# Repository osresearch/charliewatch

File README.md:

"Analog" watch with 60+12 Charlieplexed LEDs. Based on Travis Goodspeed's
GoodWatch21 schematic, using the CC430F5137IRGZR CPU, which doesn't
have the LCD controller of the CC430F6xxx in the GoodWatch. There are
also pads for a six pin EZfet cable with pogopins for programming or
serial communication.

v0.2 works, although it has no radio parts.  It is exactly 1 square inch
of PCB and should fit in a 38mm or 36mm case.

v0.1 works, although the radio parts have not been tested.  It is a slightly
larger board and fits in a 40mm case.

[Charliewtch schematic](datasheets/charliewatch.pdf)

Building the firmware
-----

Note: some other system packages (boost libraries?) might also be needed.

First, get the toolchain (msp430-gcc):

    sudo apt install gcc-msp430 mspdebug

Then the all-important lib file (from https://www.ti.com/tool/MSPDS):

    sudo apt install libhidapi-dev
    mkdir MSPDebugStack
    wget https://software-dl.ti.com/msp430/msp430_public_sw/mcu/msp430/MSPDS/3_15_1_001/export/MSPDebugStack_OS_Package_3_15_1_1.zip

Copy in the hidapi header (WTFBBQ):

    cp /usr/include/hidapi/hidapi.h ThirdParty/include/

Copy the following into a file 'hidapi.patch', so we can use the system hidapi library:

    --- Makefile    2020-12-18 18:01:18.602942502 +0100
    +++ Makefile.new    2020-12-18 18:02:58.472096541 +0100
    @@ -123,7 +123,7 @@
     OBJS := $(patsubst %.cpp, %.o, $(SRC))
    
     all: $(BSLLIB) $(OBJS)
    -   $(CXX) $(CXXFLAGS) -shared $(OUTNAME)$(OUTPUT) -o $(OUTPUT) $(OBJS) $(HIDOBJ) $(LIBDIRS) $(BSTATIC) $(STATIC_LIBS) $(BDYNAMIC) $(LIBS)
    +   $(CXX) $(CXXFLAGS) -shared $(OUTNAME)$(OUTPUT) -o $(OUTPUT) $(OBJS) -lhidapi-libusb $(LIBDIRS) $(BSTATIC) $(STATIC_LIBS) $(BDYNAMIC) $(LIBS)
        rm -f $(STATICOUTPUT).a
        ar -rs $(STATICOUTPUT).a $(OBJS)

Then apply and make:

    patch < hidapi.patch
    make

Finally, build and flash the firmware:

    git clone https://github.com/osresearch/charliewatch.git
    cd charliewatch/firmware
    make
    export LD_LIBRARY_PATH=$LD_LIBRARY_PATH:`pwd`../../MSPDebugStack/
    mspdebug tilib "prog charliewatch.elf"

Programming cable
-----

From the top of the v0.1 board:
* RST / TDIO
* RXD on programmer
* TXD on programmer
* VCC
* TST / TCK
* GND

v0.2:
* greem
* white
* blue
* purple
* gray
* black

There is also a four-wire setup that might simplify the wiring.
Travis documents it and the power consumption here:
https://github.com/travisgoodspeed/goodwatch/wiki/EnergyTrace

Bricked Launchpad
-----

If you brick your launchpad by running Energia under Linux, it will no
longer program the Charliewatch.  The other weirdness is that `tilib`
can detect the device, but can't write to it unless run as root.

Energy Trace
----
* `libmsp430.so`: https://dlbeer.co.nz/articles/slac460y/index.html
* https://github.com/carrotIndustries/energytrace-util
* Have to update path to `MSP430.h` from the `slac/DLL430_v3/include` directory

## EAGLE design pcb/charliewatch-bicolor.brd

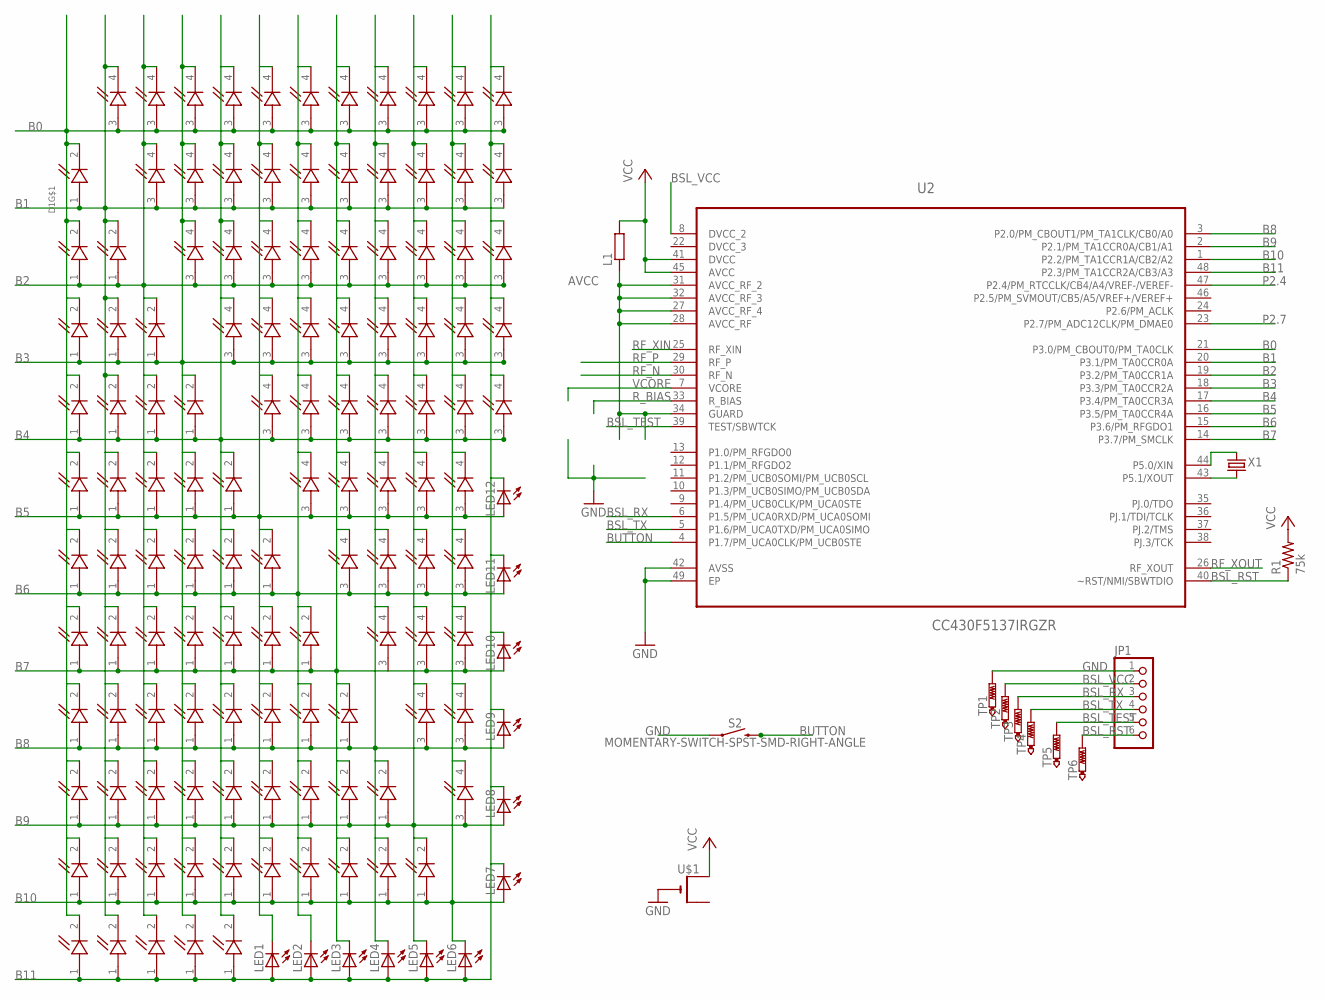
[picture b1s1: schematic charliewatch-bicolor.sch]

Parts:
D1, D2, D3, D4, D5, D6, D7, D8, D9, D10, D11, D12, D13, D14, D15, D16, D17, D18, D19, D20, D21, D22, D23, D24, D25, D26, D27, D28, D29, D30, D31, D32, D33, D34, D35, D36, D37, D38, D39, D40, D41, D42, D43, D44, D45, D46, D47, D48, D49, D50, D51, D52, D53, D54, D55, D56, D57, D58, D59, D60: APHB1608SYKSURKC; LED_APHB1608SYKSURKC
JP1: PINHD-1X6LOCK; 1X06-BIGLOCK
L1: R-EU_R0603; R0603
LED1, LED2, LED3, LED4, LED5, LED6, LED7, LED8, LED9, LED10, LED11, LED12: LEDCHIPLED_0805; CHIPLED_0805
R1: 75k; R0402
S2: MOMENTARY-SWITCH-SPST-SMD-RIGHT-ANGLE; TACTILE_SWITCH_SMD_RIGHT_ANGLE
TP1: PTR1TP10SQ; TP10SQ
TP2, TP3, TP4, TP5, TP6: PTR1TP10R; TP10R
U2: CC430F5137IRGZR; QFN50P700X700X100-49N
U$1: CR2032THM; CR2032-THRU
X1: CRYSTALS-NOGND-IQXC-25; 2.0X1.2-2PAD

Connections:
AVCC: L1.1, U2.27 (AVCC_RF_4), U2.28 (AVCC_RF), U2.31 (AVCC_RF_2), U2.32 (AVCC_RF_3), U2.34 (GUARD)
B0: D1.2 (Y_C), D1.3 (R_A), D2.2 (Y_C), D2.3 (R_A), D3.2 (Y_C), D3.3 (R_A), D5.2 (Y_C), D5.3 (R_A), D7.2 (Y_C), D7.3 (R_A), D10.2 (Y_C), D10.3 (R_A), D13.2 (Y_C), D13.3 (R_A), D17.2 (Y_C), D17.3 (R_A), D21.2 (Y_C), D21.3 (R_A), D26.2 (Y_C), D26.3 (R_A), D31.2 (Y_C), D31.3 (R_A), U2.21 (P3.0/PM_CBOUT0/PM_TA0CLK)
B1: D1.1 (Y_A), D1.4 (R_C), D4.2 (Y_C), D4.3 (R_A), D6.2 (Y_C), D6.3 (R_A), D8.2 (Y_C), D8.3 (R_A), D11.2 (Y_C), D11.3 (R_A), D14.2 (Y_C), D14.3 (R_A), D18.2 (Y_C), D18.3 (R_A), D22.2 (Y_C), D22.3 (R_A), D27.2 (Y_C), D27.3 (R_A), D32.2 (Y_C), D32.3 (R_A), D37.2 (Y_C), D37.3 (R_A), U2.20 (P3.1/PM_TA0CCR0A)
B2: D2.1 (Y_A), D2.4 (R_C), D4.1 (Y_A), D4.4 (R_C), D9.2 (Y_C), D9.3 (R_A), D12.2 (Y_C), D12.3 (R_A), D15.2 (Y_C), D15.3 (R_A), D19.2 (Y_C), D19.3 (R_A), D23.2 (Y_C), D23.3 (R_A), D28.2 (Y_C), D28.3 (R_A), D33.2 (Y_C), D33.3 (R_A), D38.2 (Y_C), D38.3 (R_A), D42.2 (Y_C), D42.3 (R_A), U2.19 (P3.2/PM_TA0CCR1A)
B3: D3.1 (Y_A), D3.4 (R_C), D6.1 (Y_A), D6.4 (R_C), D9.1 (Y_A), D9.4 (R_C), D16.2 (Y_C), D16.3 (R_A), D20.2 (Y_C), D20.3 (R_A), D24.2 (Y_C), D24.3 (R_A), D29.2 (Y_C), D29.3 (R_A), D34.2 (Y_C), D34.3 (R_A), D39.2 (Y_C), D39.3 (R_A), D43.2 (Y_C), D43.3 (R_A), D47.2 (Y_C), D47.3 (R_A), U2.18 (P3.3/PM_TA0CCR2A)
B4: D5.1 (Y_A), D5.4 (R_C), D8.1 (Y_A), D8.4 (R_C), D12.1 (Y_A), D12.4 (R_C), D16.1 (Y_A), D16.4 (R_C), D25.2 (Y_C), D25.3 (R_A), D30.2 (Y_C), D30.3 (R_A), D35.2 (Y_C), D35.3 (R_A), D40.2 (Y_C), D40.3 (R_A), D44.2 (Y_C), D44.3 (R_A), D48.2 (Y_C), D48.3 (R_A), D51.2 (Y_C), D51.3 (R_A), U2.17 (P3.4/PM_TA0CCR3A)
B5: D7.1 (Y_A), D7.4 (R_C), D11.1 (Y_A), D11.4 (R_C), D15.1 (Y_A), D15.4 (R_C), D20.1 (Y_A), D20.4 (R_C), D25.1 (Y_A), D25.4 (R_C), D36.2 (Y_C), D36.3 (R_A), D41.2 (Y_C), D41.3 (R_A), D45.2 (Y_C), D45.3 (R_A), D49.2 (Y_C), D49.3 (R_A), D52.2 (Y_C), D52.3 (R_A), LED1.C, LED12.A, U2.16 (P3.5/PM_TA0CCR4A)
B6: D10.1 (Y_A), D10.4 (R_C), D14.1 (Y_A), D14.4 (R_C), D19.1 (Y_A), D19.4 (R_C), D24.1 (Y_A), D24.4 (R_C), D30.1 (Y_A), D30.4 (R_C), D36.1 (Y_A), D36.4 (R_C), D46.2 (Y_C), D46.3 (R_A), D50.2 (Y_C), D50.3 (R_A), D53.2 (Y_C), D53.3 (R_A), D56.2 (Y_C), D56.3 (R_A), LED2.C, LED11.A, U2.15 (P3.6/PM_RFGDO1)
B7: D13.1 (Y_A), D13.4 (R_C), D18.1 (Y_A), D18.4 (R_C), D23.1 (Y_A), D23.4 (R_C), D29.1 (Y_A), D29.4 (R_C), D35.1 (Y_A), D35.4 (R_C), D41.1 (Y_A), D41.4 (R_C), D46.1 (Y_A), D46.4 (R_C), D54.2 (Y_C), D57.2 (Y_C), D57.3 (R_A), D59.2 (Y_C), D59.3 (R_A), LED10.A, U2.14 (P3.7/PM_SMCLK)
B8: D17.1 (Y_A), D17.4 (R_C), D22.1 (Y_A), D22.4 (R_C), D28.1 (Y_A), D28.4 (R_C), D34.1 (Y_A), D34.4 (R_C), D40.1 (Y_A), D40.4 (R_C), D45.1 (Y_A), D45.4 (R_C), D50.1 (Y_A), D50.4 (R_C), D54.1 (Y_A), D54.4 (R_C), D55.2 (Y_C), D55.3 (R_A), D60.2 (Y_C), D60.3 (R_A), LED9.A, U2.3 (P2.0/PM_CBOUT1/PM_TA1CLK/CB0/A0)
B9: D21.1 (Y_A), D21.4 (R_C), D27.1 (Y_A), D27.4 (R_C), D33.1 (Y_A), D33.4 (R_C), D39.1 (Y_A), D39.4 (R_C), D44.1 (Y_A), D44.4 (R_C), D49.1 (Y_A), D49.4 (R_C), D53.1 (Y_A), D53.4 (R_C), D57.1 (Y_A), D57.4 (R_C), D58.2 (Y_C), D58.3 (R_A), D60.1 (Y_A), D60.4 (R_C), LED8.A, U2.2 (P2.1/PM_TA1CCR0A/CB1/A1)
B10: D26.1 (Y_A), D26.4 (R_C), D32.1 (Y_A), D32.4 (R_C), D38.1 (Y_A), D38.4 (R_C), D43.1 (Y_A), D43.4 (R_C), D48.1 (Y_A), D48.4 (R_C), D52.1 (Y_A), D52.4 (R_C), D55.1 (Y_A), D55.4 (R_C), D56.1 (Y_A), D56.4 (R_C), D58.1 (Y_A), D58.4 (R_C), D59.1 (Y_A), D59.4 (R_C), LED7.A, U2.1 (P2.2/PM_TA1CCR1A/CB2/A2)
B11: D31.1 (Y_A), D31.4 (R_C), D37.1 (Y_A), D37.4 (R_C), D42.1 (Y_A), D42.4 (R_C), D47.1 (Y_A), D47.4 (R_C), D51.1 (Y_A), D51.4 (R_C), LED1.A, LED2.A, LED3.A, LED4.A, LED5.A, LED6.A, U2.48 (P2.3/PM_TA1CCR2A/CB3/A3)
BSL_RST: JP1.6, R1.1, TP6.TP, U2.40 (~RST/NMI/SBWTDIO)
BSL_RX: JP1.3, TP3.TP, U2.6 (P1.5/PM_UCA0RXD/PM_UCA0SOMI)
BSL_TEST: JP1.5, TP5.TP, U2.39 (TEST/SBWTCK)
BSL_TX: JP1.4, TP4.TP, U2.5 (P1.6/PM_UCA0TXD/PM_UCA0SIMO)
BSL_VCC: JP1.2, TP2.TP, U2.8 (DVCC_2)
BUTTON: S2.2, U2.4 (P1.7/PM_UCA0CLK/PM_UCB0STE)
DVCC_3: U2.22 (DVCC_3)
GND: JP1.1, S2.1, TP1.TP, U2.42 (AVSS), U2.49 (EP), U$1.-
P2.4: U2.47 (P2.4/PM_RTCCLK/CB4/A4/VREF-/VEREF-)
P2.7: U2.23 (P2.7/PM_ADC12CLK/PM_DMAE0)
RF_N: U2.30 (RF_N)
RF_P: U2.29 (RF_P)
RF_XIN: U2.25 (RF_XIN)
RF_XOUT: U2.26 (RF_XOUT)
R_BIAS: U2.33 (R_BIAS)
VCC: L1.2, R1.2, U2.41 (DVCC), U2.45 (AVCC), U$1.+1 (+)
VCORE: U2.7 (VCORE)
XIN: U2.44 (P5.0/XIN), X1.2
XOUT: U2.43 (P5.1/XOUT), X1.1

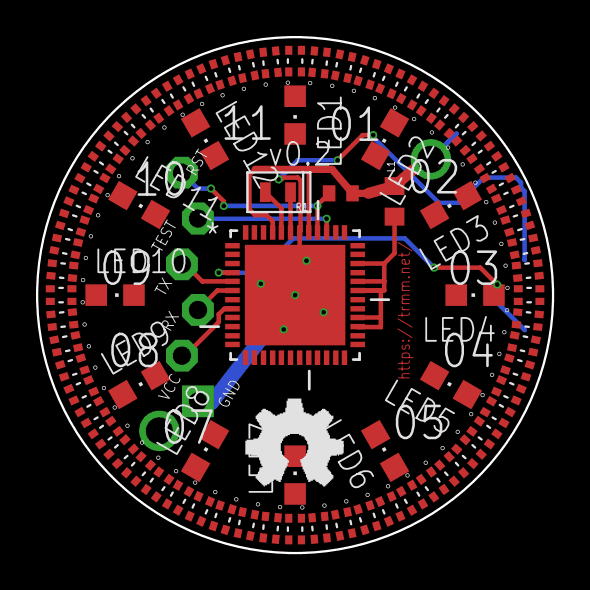
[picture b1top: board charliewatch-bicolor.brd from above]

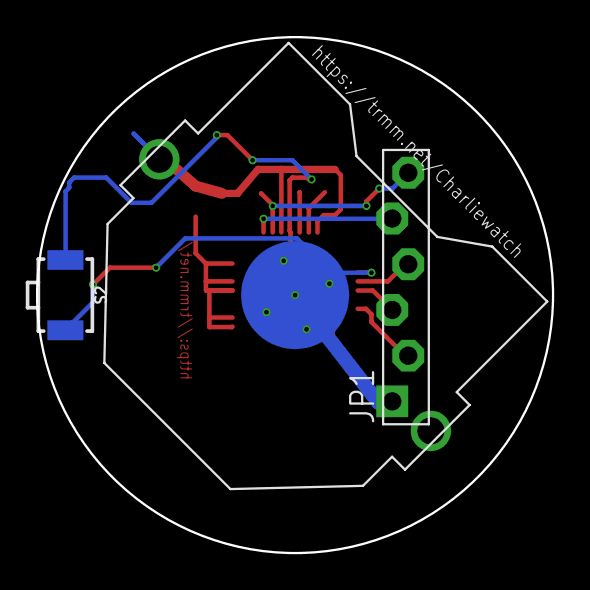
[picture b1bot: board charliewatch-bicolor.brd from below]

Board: 2 copper layers, 28.7 x 28.7 mm, 85 parts (3 on the bottom side), 23 nets.

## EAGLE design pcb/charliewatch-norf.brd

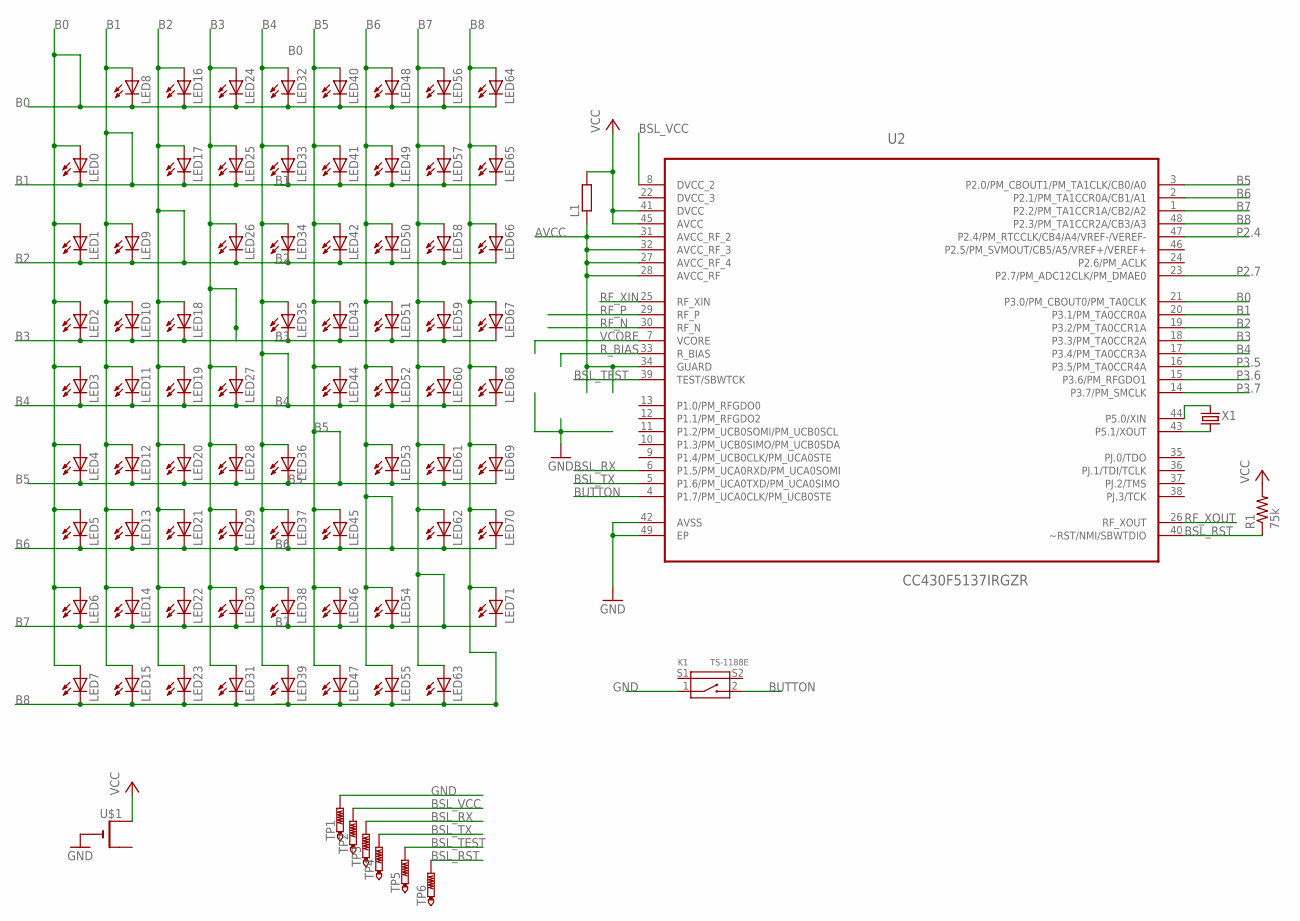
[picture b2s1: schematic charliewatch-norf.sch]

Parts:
K1: TS-1188E; SW4-SMD-7.0X3.5X3.5MM-90D
L1: R-EU_R0603; R0603
LED0, LED1, LED2, LED3, LED4, LED5, LED6, LED7, LED8, LED9, LED10, LED11, LED12, LED13, LED14, LED15, LED16, LED17, LED18, LED19, LED20, LED21, LED22, LED23, LED24, LED25, LED26, LED27, LED28, LED29, LED30, LED31, LED32, LED33, LED34, LED35, LED36, LED37, LED38, LED39, LED40, LED41, LED42, LED43, LED44, LED45, LED46, LED47, LED48, LED49, LED50, LED51, LED52, LED53, LED54, LED55, LED56, LED57, LED58, LED59, LED60, LED61, LED62, LED63, LED64, LED65, LED66, LED67, LED68, LED69, LED70, LED71: LEDCHIPLED_0603; CHIPLED_0603
R1: 75k; R0402
TP1: PTR1TP10SQ; TP10SQ
TP2, TP3, TP4, TP5, TP6: PTR1TP10R; TP10R
U2: CC430F5137IRGZR; QFN50P700X700X100-49N
U$1: CR2032SMT; CR2032-SMD
X1: CRYSTALS-NOGND-IQXC-25; 2.0X1.2-2PAD

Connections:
AVCC: L1.1, U2.27 (AVCC_RF_4), U2.28 (AVCC_RF), U2.31 (AVCC_RF_2), U2.32 (AVCC_RF_3), U2.34 (GUARD)
B0: LED0.A, LED1.A, LED2.A, LED3.A, LED4.A, LED5.A, LED6.A, LED7.A, LED8.C, LED16.C, LED24.C, LED32.C, LED40.C, LED48.C, LED56.C, LED64.C, U2.21 (P3.0/PM_CBOUT0/PM_TA0CLK)
B1: LED0.C, LED8.A, LED9.A, LED10.A, LED11.A, LED12.A, LED13.A, LED14.A, LED15.A, LED17.C, LED25.C, LED33.C, LED41.C, LED49.C, LED57.C, LED65.C, U2.20 (P3.1/PM_TA0CCR0A)
B2: LED1.C, LED9.C, LED16.A, LED17.A, LED18.A, LED19.A, LED20.A, LED21.A, LED22.A, LED23.A, LED26.C, LED34.C, LED42.C, LED50.C, LED58.C, LED66.C, U2.19 (P3.2/PM_TA0CCR1A)
B3: LED2.C, LED10.C, LED18.C, LED24.A, LED25.A, LED26.A, LED27.A, LED28.A, LED29.A, LED30.A, LED31.A, LED35.C, LED43.C, LED51.C, LED59.C, LED67.C, U2.18 (P3.3/PM_TA0CCR2A)
B4: LED3.C, LED11.C, LED19.C, LED27.C, LED32.A, LED33.A, LED34.A, LED35.A, LED36.A, LED37.A, LED38.A, LED39.A, LED44.C, LED52.C, LED60.C, LED68.C, U2.17 (P3.4/PM_TA0CCR3A)
B5: LED4.C, LED12.C, LED20.C, LED28.C, LED36.C, LED40.A, LED41.A, LED42.A, LED43.A, LED44.A, LED45.A, LED46.A, LED47.A, LED53.C, LED61.C, LED69.C, U2.3 (P2.0/PM_CBOUT1/PM_TA1CLK/CB0/A0)
B6: LED5.C, LED13.C, LED21.C, LED29.C, LED37.C, LED45.C, LED48.A, LED49.A, LED50.A, LED51.A, LED52.A, LED53.A, LED54.A, LED55.A, LED62.C, LED70.C, U2.2 (P2.1/PM_TA1CCR0A/CB1/A1)
B7: LED6.C, LED14.C, LED22.C, LED30.C, LED38.C, LED46.C, LED54.C, LED56.A, LED57.A, LED58.A, LED59.A, LED60.A, LED61.A, LED62.A, LED63.A, LED71.C, U2.1 (P2.2/PM_TA1CCR1A/CB2/A2)
B8: LED7.C, LED15.C, LED23.C, LED31.C, LED39.C, LED47.C, LED55.C, LED63.C, LED64.A, LED65.A, LED66.A, LED67.A, LED68.A, LED69.A, LED70.A, LED71.A, U2.48 (P2.3/PM_TA1CCR2A/CB3/A3)
BSL_RST: R1.1, TP6.TP, U2.40 (~RST/NMI/SBWTDIO)
BSL_RX: TP3.TP, U2.6 (P1.5/PM_UCA0RXD/PM_UCA0SOMI)
BSL_TEST: TP5.TP, U2.39 (TEST/SBWTCK)
BSL_TX: TP4.TP, U2.5 (P1.6/PM_UCA0TXD/PM_UCA0SIMO)
BSL_VCC: TP2.TP, U2.8 (DVCC_2)
BUTTON: K1.2, U2.4 (P1.7/PM_UCA0CLK/PM_UCB0STE)
DVCC_3: U2.22 (DVCC_3)
GND: K1.1, TP1.TP, U2.42 (AVSS), U2.49 (EP), U$1.-
P2.4: U2.47 (P2.4/PM_RTCCLK/CB4/A4/VREF-/VEREF-)
P2.7: U2.23 (P2.7/PM_ADC12CLK/PM_DMAE0)
P3.5: U2.16 (P3.5/PM_TA0CCR4A)
P3.6: U2.15 (P3.6/PM_RFGDO1)
P3.7: U2.14 (P3.7/PM_SMCLK)
RF_N: U2.30 (RF_N)
RF_P: U2.29 (RF_P)
RF_XIN: U2.25 (RF_XIN)
RF_XOUT: U2.26 (RF_XOUT)
R_BIAS: U2.33 (R_BIAS)
VCC: L1.2, R1.2, U2.41 (DVCC), U2.45 (AVCC), U$1.+$1 (+)
VCORE: U2.7 (VCORE)
XIN: U2.44 (P5.0/XIN), X1.2
XOUT: U2.43 (P5.1/XOUT), X1.1

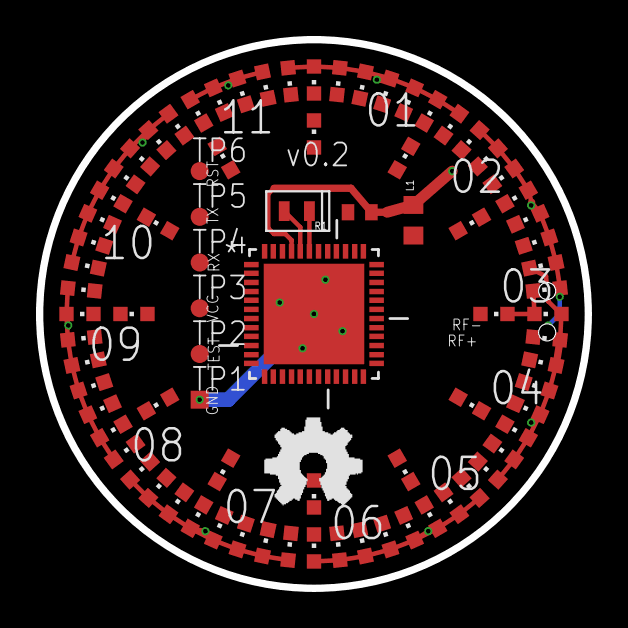
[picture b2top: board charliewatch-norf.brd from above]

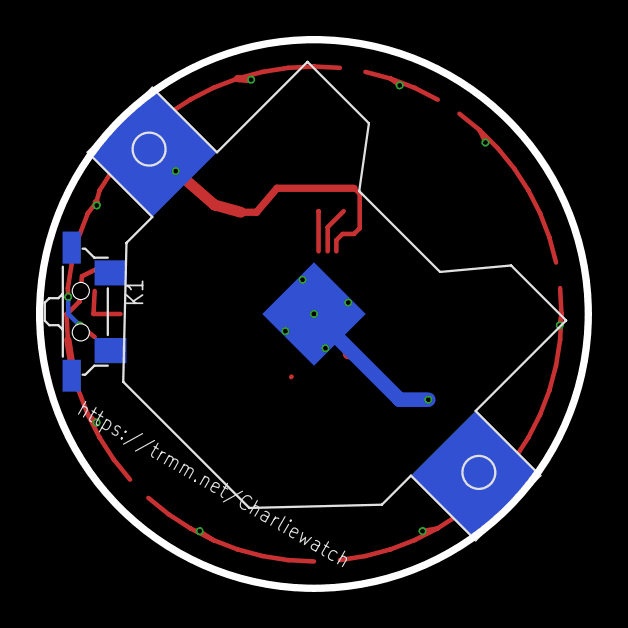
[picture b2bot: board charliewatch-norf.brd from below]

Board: 2 copper layers, 30.5 x 30.5 mm, 84 parts (2 on the bottom side), 20 nets.

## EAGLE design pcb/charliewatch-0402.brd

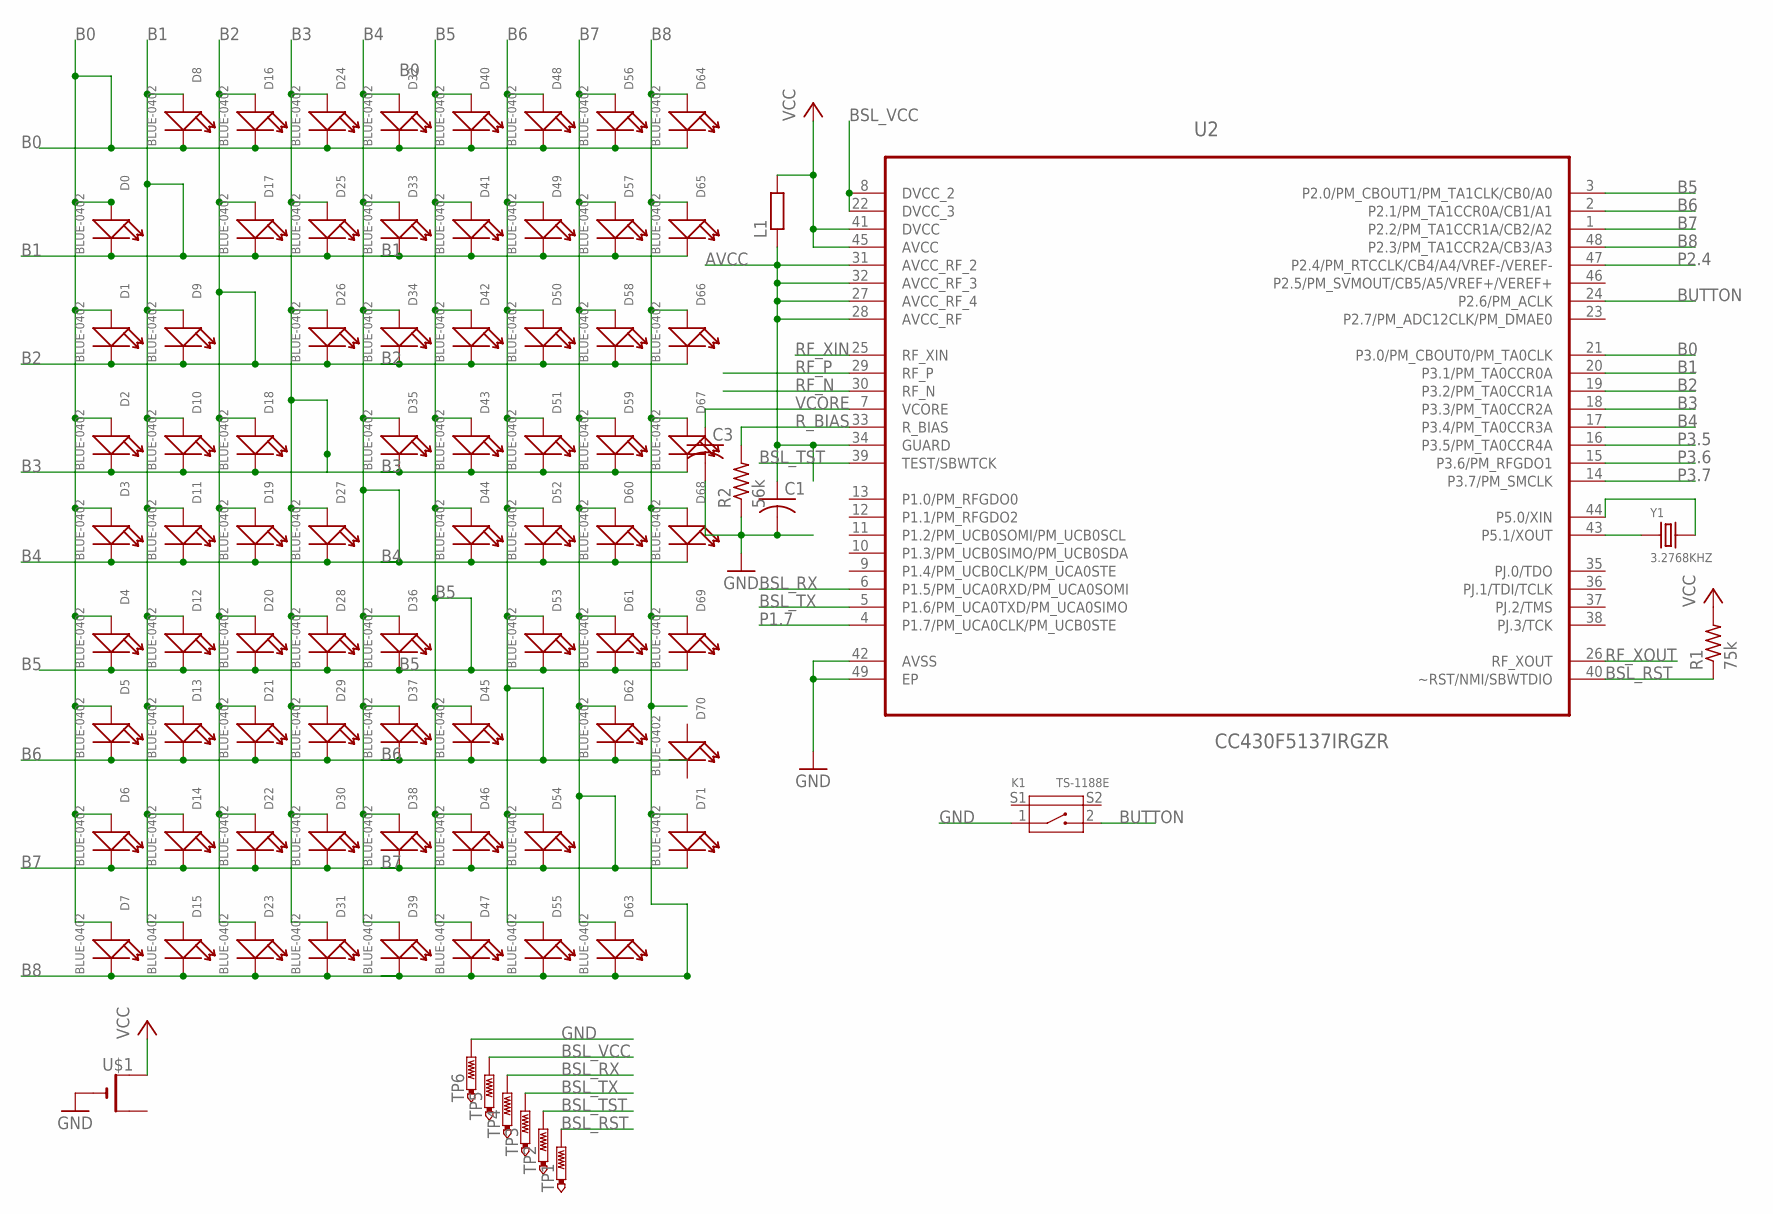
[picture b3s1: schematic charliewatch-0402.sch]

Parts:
C1, C3: C-USC0402; C0402
D0, D1, D2, D3, D4, D5, D6, D7, D8, D9, D10, D11, D12, D13, D14, D15, D16, D17, D18, D19, D20, D21, D22, D23, D24, D25, D26, D27, D28, D29, D30, D31, D32, D33, D34, D35, D36, D37, D38, D39, D40, D41, D42, D43, D44, D45, D46, D47, D48, D49, D50, D51, D52, D53, D54, D55, D56, D57, D58, D59, D60, D61, D62, D63, D64, D65, D66, D67, D68, D69, D70, D71: BLUE-0402; LED-0402
K1: TS-1188E; SW4-SMD-7.0X3.5X3.5MM-90D
L1: R-EU_R0603; R0603
R1: 75k; R0402
R2: 56k; R0402
TP1, TP2, TP3, TP4, TP5: PTR1TP10R; TP10R
TP6: PTR1TP10SQ; TP10SQ
U2: CC430F5137IRGZR; QFN50P700X700X100-49N
U$1: CR2032SMT; CR2032-SMD
Y1: 3.2768KHZ; X2-SMD-L2.0X1.2X0.55MM

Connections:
AVCC: C1.1, L1.1, U2.27 (AVCC_RF_4), U2.28 (AVCC_RF), U2.31 (AVCC_RF_2), U2.32 (AVCC_RF_3), U2.34 (GUARD)
B0: D0.+, D1.+, D2.+, D3.+, D4.+, D5.+, D6.+, D7.+, D8.-, D16.-, D24.-, D32.-, D40.-, D48.-, D56.-, D64.-, U2.21 (P3.0/PM_CBOUT0/PM_TA0CLK)
B1: D0.-, D8.+, D9.+, D10.+, D11.+, D12.+, D13.+, D14.+, D15.+, D17.-, D25.-, D33.-, D41.-, D49.-, D57.-, D65.-, U2.20 (P3.1/PM_TA0CCR0A)
B2: D1.-, D9.-, D16.+, D17.+, D18.+, D19.+, D20.+, D21.+, D22.+, D23.+, D26.-, D34.-, D42.-, D50.-, D58.-, D66.-, U2.19 (P3.2/PM_TA0CCR1A)
B3: D2.-, D10.-, D18.-, D24.+, D25.+, D26.+, D27.+, D28.+, D29.+, D30.+, D31.+, D35.-, D43.-, D51.-, D59.-, D67.-, U2.18 (P3.3/PM_TA0CCR2A)
B4: D3.-, D11.-, D19.-, D27.-, D32.+, D33.+, D34.+, D35.+, D36.+, D37.+, D38.+, D39.+, D44.-, D52.-, D60.-, D68.-, U2.17 (P3.4/PM_TA0CCR3A)
B5: D4.-, D12.-, D20.-, D28.-, D36.-, D40.+, D41.+, D42.+, D43.+, D44.+, D45.+, D46.+, D47.+, D53.-, D61.-, D69.-, U2.3 (P2.0/PM_CBOUT1/PM_TA1CLK/CB0/A0)
B6: D5.-, D13.-, D21.-, D29.-, D37.-, D45.-, D48.+, D49.+, D50.+, D51.+, D52.+, D53.+, D54.+, D55.+, D62.-, U2.2 (P2.1/PM_TA1CCR0A/CB1/A1)
B7: D6.-, D14.-, D22.-, D30.-, D38.-, D46.-, D54.-, D56.+, D57.+, D58.+, D59.+, D60.+, D61.+, D62.+, D63.+, D71.-, U2.1 (P2.2/PM_TA1CCR1A/CB2/A2)
B8: D7.-, D15.-, D23.-, D31.-, D39.-, D47.-, D55.-, D63.-, D64.+, D65.+, D66.+, D67.+, D68.+, D69.+, D71.+, U2.48 (P2.3/PM_TA1CCR2A/CB3/A3)
BSL_RST: R1.1, TP1.TP, U2.40 (~RST/NMI/SBWTDIO)
BSL_RX: TP4.TP, U2.6 (P1.5/PM_UCA0RXD/PM_UCA0SOMI)
BSL_TST: TP2.TP, U2.39 (TEST/SBWTCK)
BSL_TX: TP3.TP, U2.5 (P1.6/PM_UCA0TXD/PM_UCA0SIMO)
BSL_VCC: TP5.TP, U2.8 (DVCC_2), U2.22 (DVCC_3)
BUTTON: K1.2, U2.24 (P2.6/PM_ACLK)
GND: C1.2, C3.2, K1.1, R2.1, TP6.TP, U2.42 (AVSS), U2.49 (EP), U$1.-
P1.7: U2.4 (P1.7/PM_UCA0CLK/PM_UCB0STE)
P2.4: U2.47 (P2.4/PM_RTCCLK/CB4/A4/VREF-/VEREF-)
P3.5: U2.16 (P3.5/PM_TA0CCR4A)
P3.6: U2.15 (P3.6/PM_RFGDO1)
P3.7: U2.14 (P3.7/PM_SMCLK)
RF_N: U2.30 (RF_N)
RF_P: U2.29 (RF_P)
RF_XIN: U2.25 (RF_XIN)
RF_XOUT: U2.26 (RF_XOUT)
R_BIAS: R2.2, U2.33 (R_BIAS)
VCC: L1.2, R1.2, U2.41 (DVCC), U2.45 (AVCC), U$1.+$1 (+)
VCORE: C3.1, U2.7 (VCORE)
XIN: U2.44 (P5.0/XIN), Y1.2
XOUT: U2.43 (P5.1/XOUT), Y1.1

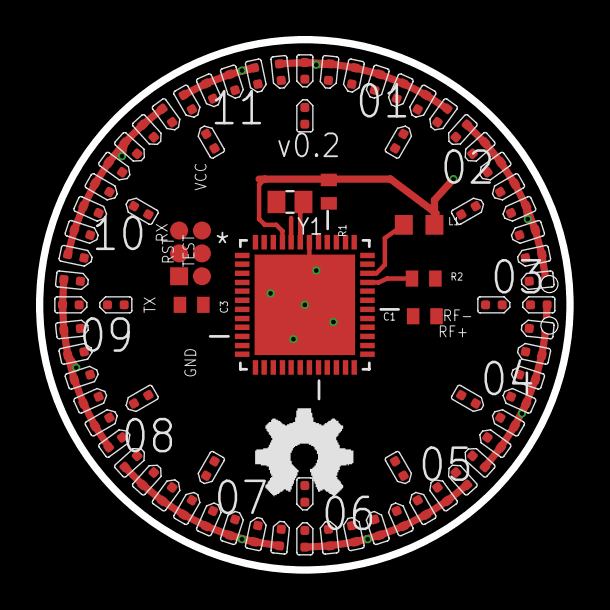
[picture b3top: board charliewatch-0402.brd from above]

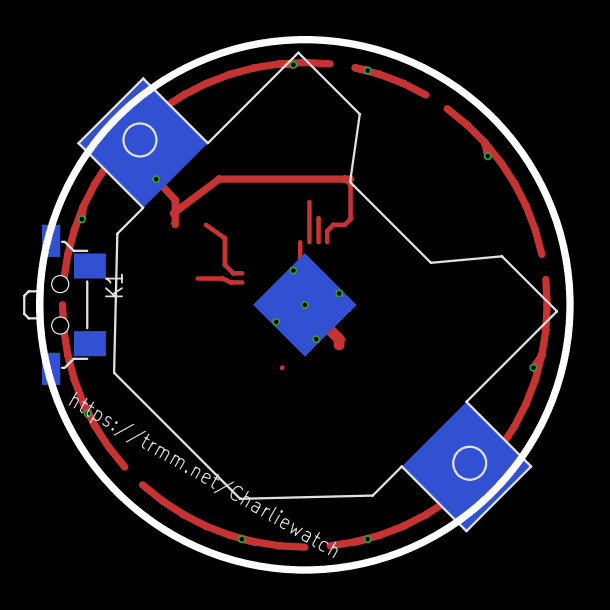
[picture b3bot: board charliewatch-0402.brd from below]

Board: 2 copper layers, 29.5 x 29.5 mm, 87 parts (2 on the bottom side), 22 nets.

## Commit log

2018-09-27 v0 board autoroutes 100%
2018-09-27 fixed drc errors, one missing vcc pin
2018-09-27 move labels and 1x6 around; issues with the additional vcc line
2018-09-27 replace with "1x6 lock" part
2018-09-27 ignore temp files
2018-09-27 tweaked text, added oshw logo
2018-09-27 as orderd v0.1
2018-09-28 datasheets
2018-09-28 readme and rendering
2018-09-28 v0.1 image, as ordered
2018-09-28 ignore routed schematic, which sould not be checked in
2018-09-28 v0.1 schematic
2018-10-13 blink all the led test
2018-10-13 ignore generated files
2018-10-13 import of the goodwatch Makefile, with updates
2018-10-13 blink test work again
2018-10-13 remove unnecesary run
2018-10-13 try different brightnesses
2018-10-13 pwm brightness works
2018-10-13 import RTC code from goodwatch; sleep most of the time
2018-10-13 tweak timings
2018-10-13 move LED code into separate file
2018-10-13 add external crystal support, but not enabled
2018-10-13 programming cable note
2018-10-13 Simple 3d printed case for testing
2018-10-13 clock display works, ramsave and romsavetime do the right thing
2018-10-13 zoom the second hand when it matches the minute hand
2018-10-13 make the case fit a CR2405 battery holder
2018-10-13 re-enable ucs_init()
2018-10-13 move build time into separate file
2018-10-13 ignore STL files
2018-10-13 use separate brightness array and make the hour brightness breath
2018-10-15 fix build time with octal leading zero issue
2018-10-15 "faster" delay loop to have finer granularity
2018-10-15 more animations for every five minutes and on the hour
2018-10-15 try ramping the clock down during the sleep (not sure if it matters)
2018-10-15 try using power_setvcore() to bring the internal voltage down to svae power
2018-10-15 energy trace notes
2018-10-15 sparkles when all three hands line up
2018-10-15 hour hand animation
2018-10-15 switch hour animation direction
2018-10-16 move animation into separate file
2018-10-16 turn off P1 to reduce even more current draw (less than 10 uA with the LEDs off)
2018-10-16 ensure that the LEDs are off before going to sleep
2018-10-16 more animations for hand alignments
2018-10-16 slow down hour hand animation so that it aligns with second hand
2018-10-17 extra animation at the top of the hour
2018-10-17 experimenting with temporal dithering on LEDs
2018-10-17 enable -Wall and fix warnings
2018-10-18 0402 sized LEDs
2018-10-18 press-fit watch face from the back
2018-10-19 no rf variant (routable)
2018-10-19 slightly smaller, still routable version with no RF components
2018-10-20 triangle time and improved sparkle
2018-10-20 routed version of the no-rf variant, with 1 square inch of board area
2018-10-21 alternate triangle animation
2018-10-21 refactor animation to use a function pointer and single counter
2018-10-21 stopwatch module
2018-10-21 button configuration and stop/reset logic works
2018-10-21 mode cycling works
2018-10-21 clock set mode (toggles between hours and minutes, with timeout)
2018-10-21 timeout from stopwatch mode
2018-10-22 fix off by one blink in opposite and triangle time
2018-10-26 sweep second hour during hour/second alignment (issue #3)
2018-10-26 make the all align animation run twice (issue #4)
2018-10-26 new minute animation (issue #2)
2018-10-26 special all align animation for six (issue #4)
2018-10-27 improve new minute animation by rewinding minute hand (issue #2)
2018-10-27 improve new minute animation by rewinding or forwarding minute hand (issue #2)
2018-10-28 v0.2 case for the smaller watch face
2018-10-29 stencil for v0.2 board (no RF components, smaller diameter)
2018-10-29 outline and alignment holes
2018-10-30 local variable for led
2018-10-30 led_test()
2018-10-30 led_dither() to reduce power, improve brightness control
2018-11-03 make band size an option
2018-11-04 images of the two board versions
2018-11-04 use a separate buildtime nonce to detect valid RTC
2018-11-04 change the brightness for different LEDs
2018-11-04 fix led test to finish sooner
2018-11-04 make button support v0.2 boards
2018-11-04 better v0.2 image
2018-11-09 fix octal date
2018-11-09 a few more test times
2018-11-09 refactor animation timing code and add diamond time
2018-11-10 consolidate diamond time, make it a bounce
2018-11-10 chase pattern for 3 and 9
2018-11-10 improve diamond time to come from the hour hand
2018-11-11 started on band design
2018-11-11 larger pieces for the strap, sizing gauge
2018-11-11 round off the case
2018-11-12 smooth out the bands a bit more
2018-11-12 dither the triangle pattern
2018-11-12 full band and case works for rev 0.2 boards
2018-11-12 triangle test
2018-11-12 measure battery voltage and draw a bar graph
2018-11-13 taper the band
2018-11-13 fix spacing on lug
2018-11-22 v0.2 nato strap version (18mm) with sapphire
2019-01-04 switch hour hand direction in hour/second crossing
2019-01-04 as ordered from dirtypcb
2019-02-18 fix pins for avoiding power drain
2019-05-18 started on 0603 bicolor version
2019-05-18 initial positioning for the bicolor leds
2019-05-19 change to through-hole cr2032 and hack up the layout
2020-12-18 Add build instructions for Debian
2023-12-30 hack required to build for the v2.1 boards using the msp430g2553. clocks and sleep are not yet implemented

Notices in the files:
parts and their libraries:
SparkFun-Connectors: Licensing: Creative Commons ShareAlike 4.0 International - https://creativecommons.org/licenses/by-sa/4.0
